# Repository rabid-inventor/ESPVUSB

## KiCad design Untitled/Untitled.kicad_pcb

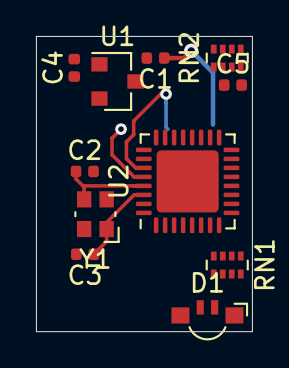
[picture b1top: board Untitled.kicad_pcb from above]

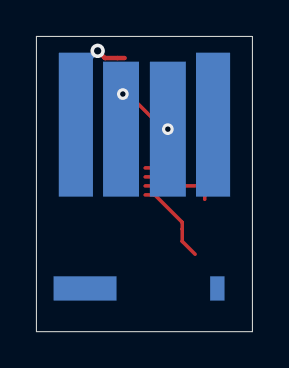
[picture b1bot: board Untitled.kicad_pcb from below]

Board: 2 copper layers, 12.0 x 16.4 mm, 13 parts (2 on the bottom side), 14 nets.

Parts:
AE1: Antenna; ACAG0801-2450Trecudedkeepout
C1, C2, C3, C4, C5: C_Small; C_0402_1005Metric
D1: LED_ARGB; LED_Kingbright_APFA3010_3x1.5mm_Horizontal
J1: USB_A; CONN-USB-A-PCB-TRACES
RN1, RN2: R_Pack04; R_Array_Concave_4x0402
U1: AP7333-33SRG-7; SOT-23
U2: ESP32-C3; QFN-32-1EP_5x5mm_P0.5mm_EP3.45x3.45mm
Y1: Crystal_GND24_Small; Crystal_SMD_Abracon_ABM10-4Pin_2.5x2.0mm

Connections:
+3V3: C4.1, D1.1, U1.2, U2.2, U2.3, U2.11, U2.17, U2.31, U2.32
/LED_B: RN1.3, U2.9
/LED_G: RN1.2, U2.8
/LED_R: RN1.1, U2.6
/USBD+: J1.3, U2.28
/USBD-: J1.2, U2.27
GND: C1.2, C2.2, C3.2, C4.2, U1.1, U2.33, Y1.2, Y1.4
unnamed: AE1.1, U2.1
unnamed: C2.1, U2.29, Y1.3
unnamed: C3.1, U2.30, Y1.1
unnamed: D1.2, RN1.8
unnamed: D1.3, RN1.7
unnamed: D1.4, RN1.6
VBUS: C1.1, J1.1, U1.3

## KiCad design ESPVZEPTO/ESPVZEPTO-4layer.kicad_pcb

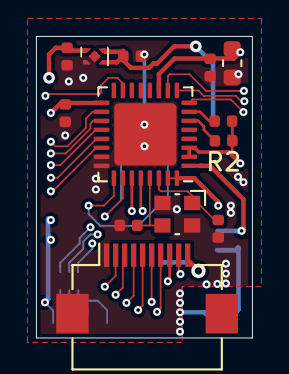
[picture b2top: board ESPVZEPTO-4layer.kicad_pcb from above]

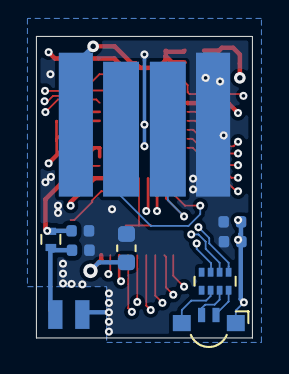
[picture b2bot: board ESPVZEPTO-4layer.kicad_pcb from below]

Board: 4 copper layers, 12.0 x 16.8 mm, 23 parts (10 on the bottom side), 25 nets.

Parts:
AE1: Antenna_Shield; Antenna-AVX-1001312
C1, C4, C5, C6, C7, C8, C11, C12: C_Small; C_0402_1005Metric
C2, C3: 10pF; C_0402_1005Metric
C9, C10: C_Small; C_0603_1608Metric
D1: LED_ARGB; LED_Kingbright_APFA3010_3x1.5mm_Horizontal
J1: USB_A; CONN-USB-A-PCB-TRACES
J2: Conn_01x10_MountingPin; Hirose_FH12-10S-0.5SH_1x10-1MP_P0.50mm_Horizontal
L1: L_Small; L_0402
R1, R2: R_Small; R_0402_1005Metric
RN1: R_Pack04; R_Array_Concave_4x0402
U1: NCP115AMX330TCG; UDFN-4_1x1mm_Pitch0.65mm
U2: ESP32-C3; QFN-32-1EP_5x5mm_P0.5mm_EP3.45x3.45mm
Y1: 40Mhz; Crystal_SMD_Abracon_ABM10-4Pin_2.5x2.0mm

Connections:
+3V3: C4.1, C5.1, C6.1, C7.1, C8.1, C9.1, C10.1, D1.1, J2.10, R1.1, R2.1, U1.1, U2.2, U2.3, U2.11, U2.17, U2.31, U2.32
/BLSEL: J2.2, U2.15
/EN: R1.2, U2.7
/GP11: J2.7, U2.18
/GP12: J2.6, U2.19
/GP13: J2.5, U2.20
/GP14: J2.4, U2.21
/GP15: J2.3, U2.22
/LED_B: RN1.3, U2.8
/LED_G: RN1.2, U2.9
/LED_R: RN1.1, U2.10
/URX: J2.8, U2.27
/USBD+: J1.3, U2.26
/USBD-: J1.2, U2.25
/UTX: J2.9, U2.28
GND: AE1.2, C1.2, C2.2, C3.2, C4.2, C5.2, C6.2, C7.2, C8.2, C9.2, C10.2, C11.1, C12.1, J1.4, J2.1, J2.MP, U1.2, U1.5, U2.23, U2.24, U2.33, Y1.2, Y1.4
unnamed: AE1.1, C11.2, L1.2
unnamed: C2.1, U2.29, Y1.3
unnamed: C3.1, U2.30, Y1.1
unnamed: C12.2, L1.1, U2.1
unnamed: D1.2, RN1.6
unnamed: D1.3, RN1.7
unnamed: D1.4, RN1.8
unnamed: R2.2, U2.6
VBUS: C1.1, J1.1, U1.3, U1.4

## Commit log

2020-12-29 first ideas
2020-12-29 update files
2021-01-08 morr work
2021-01-13 redesigned for 4 layers
2021-01-13 tweeks
2021-05-13 small tweeks and update to pin strapping
